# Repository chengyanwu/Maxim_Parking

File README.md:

# SpotOn

Description
-----------
Finding parking spots is an issue that plagues every driver. SpotOn addresses this problem by proposing an intelligent parking sensor system powered by ML image recognition. Using an onboard CNN accelerator with a microcontroller, parking spot detection can be accomplished with low cost and low power consumption. Spot statuses are sent to a central database through LoRaWAN communication and rendered on a web application for users to easily access.

Website: https://sites.google.com/view/spoton-ucsb/home

### Loading and Running Applications
OpenOCD: 
```bash
openocd -f interface/cmsis-dap.cfg -f target/max78000.cfg -s/c/MaximSDK/Tools/OpenOCD/scripts```
GDB:
```bash
arm-none-eabi-gdb max78000.elf
```
```bash
target remote localhost:3333
monitor reset halt
load
compare-sections
monitor reset halt
c
```

## LoRaWan Configuration
Device ID:
```bash
static const PROGMEM u1_t NWKSKEY[16] = { 0x82, 0xDE, 0xD9, 0x1D, 0x69, 0x58, 0xF3, 0x66, 0xBA, 0x3A, 0x8E, 0x15, 0x77, 0xA7, 0xAB, 0xD8 };  
static const u1_t PROGMEM APPSKEY[16] = { 0xDA, 0xBF, 0xD5, 0x35, 0x76, 0x48, 0x84, 0x6C, 0x0D, 0x43, 0xBD, 0xC1, 0x96, 0x54, 0x63, 0x91 };
static const u4_t DEVADDR =  0x260C8A4A ;
```

```bash
static const u1_t NWKSKEY[16] = {0x4A, 0x96, 0xDF, 0xBE, 0x3D, 0xC0, 0x7F, 0x02, 0xB3, 0xBB, 0xE2, 0xCA, 0xDB, 0x84, 0x70, 0x41};
static const u1_t APPSKEY[16] = {0x6C, 0xC5, 0x3C, 0xF2, 0x0D, 0x9A, 0x03, 0x94, 0xAB, 0x31, 0xA4, 0xE4, 0xF9, 0xE0, 0x36, 0x4F};
static const u4_t DEVADDR = 0x260CA619;
```

```bash
static const u1_t NWKSKEY[16] = {0x3A, 0x9C, 0x5C, 0x34, 0x56, 0x0C, 0x73, 0xC4, 0xF7, 0x27, 0x45, 0xDD, 0xD3, 0xC3, 0xD8, 0x9C};
static const u1_t APPSKEY[16] = {0xCE, 0xEE, 0xC9, 0x2B, 0xEB, 0x2A, 0xA8, 0x45, 0xAD, 0x2A, 0x1A, 0x33, 0x1A, 0xCC, 0xC6, 0x39};
static const u4_t DEVADDR = 0x260C6455;
```

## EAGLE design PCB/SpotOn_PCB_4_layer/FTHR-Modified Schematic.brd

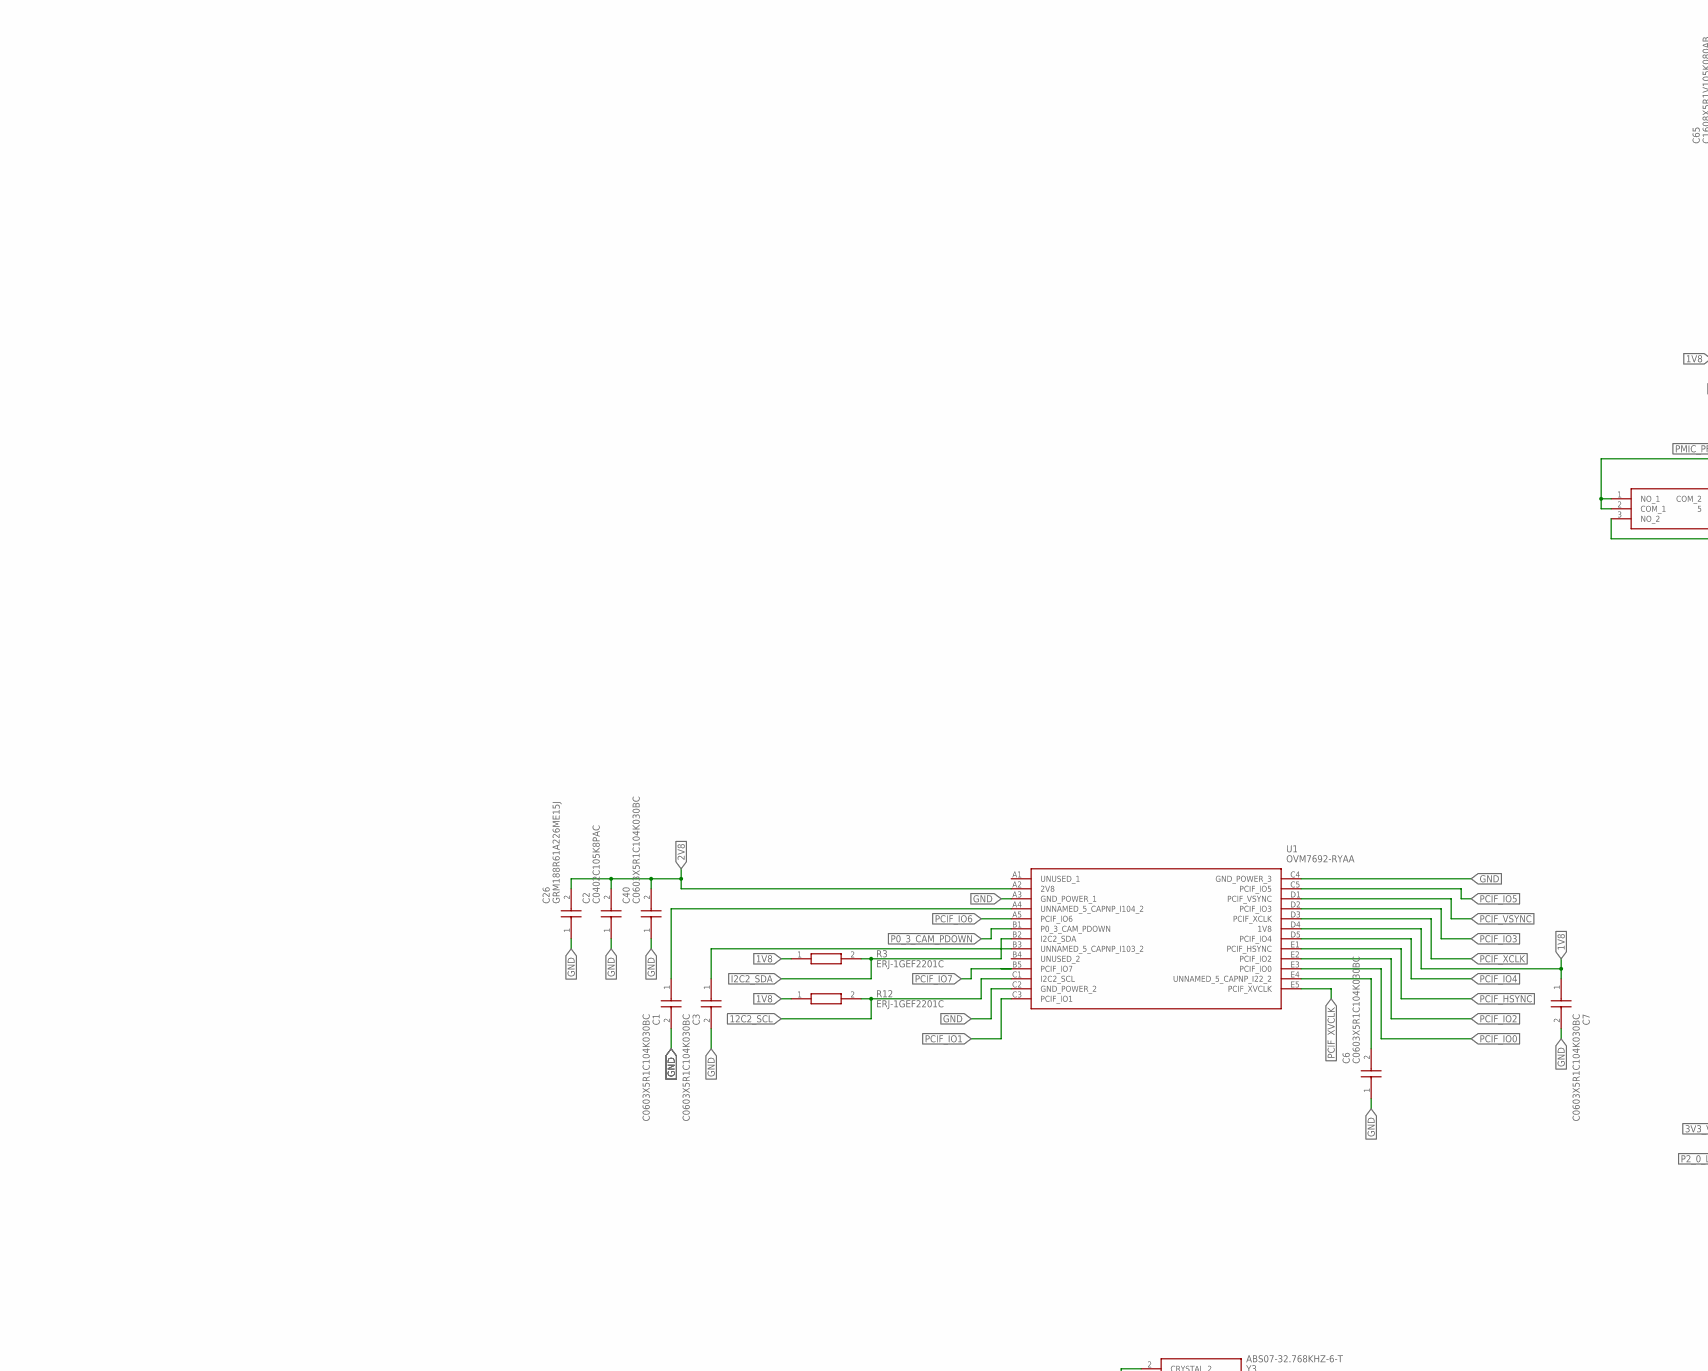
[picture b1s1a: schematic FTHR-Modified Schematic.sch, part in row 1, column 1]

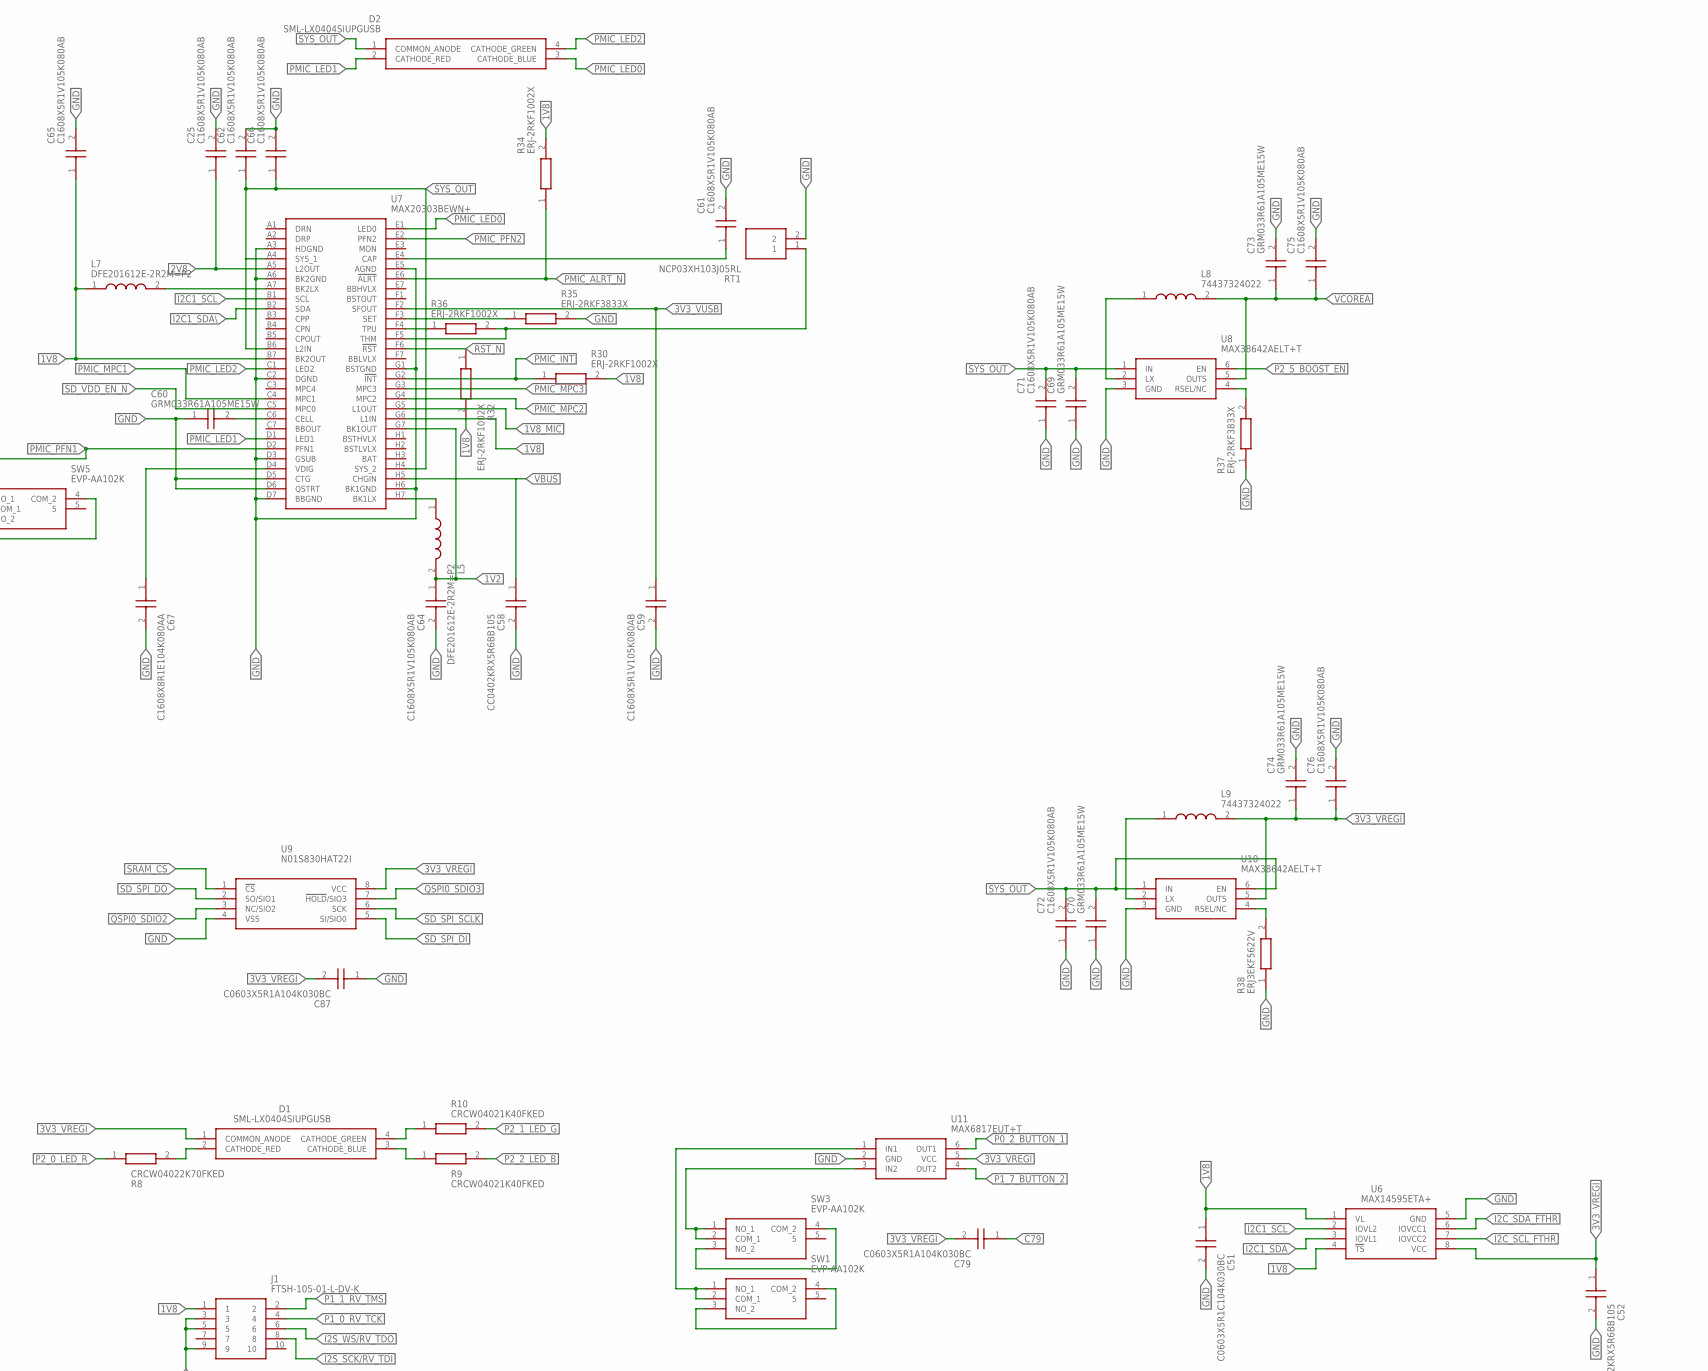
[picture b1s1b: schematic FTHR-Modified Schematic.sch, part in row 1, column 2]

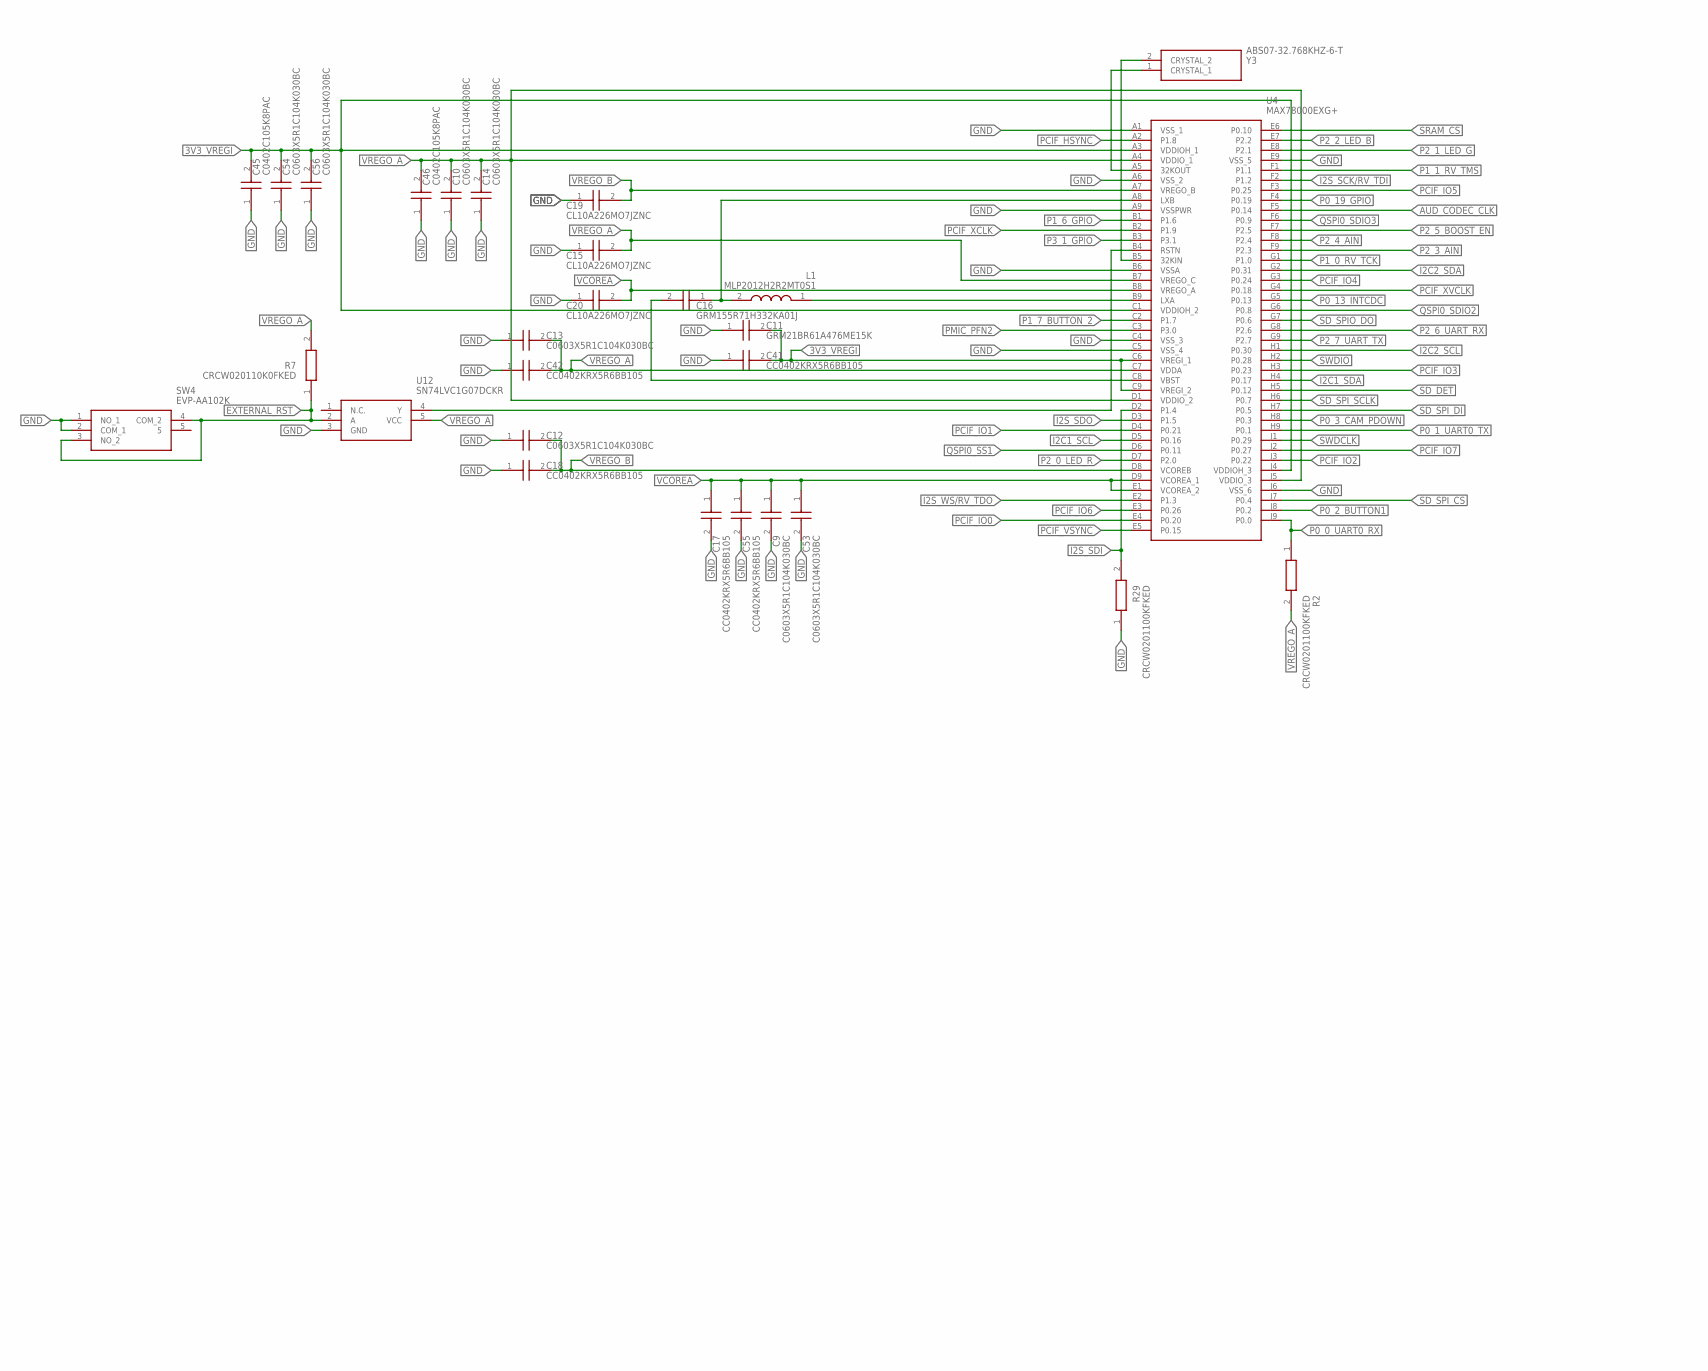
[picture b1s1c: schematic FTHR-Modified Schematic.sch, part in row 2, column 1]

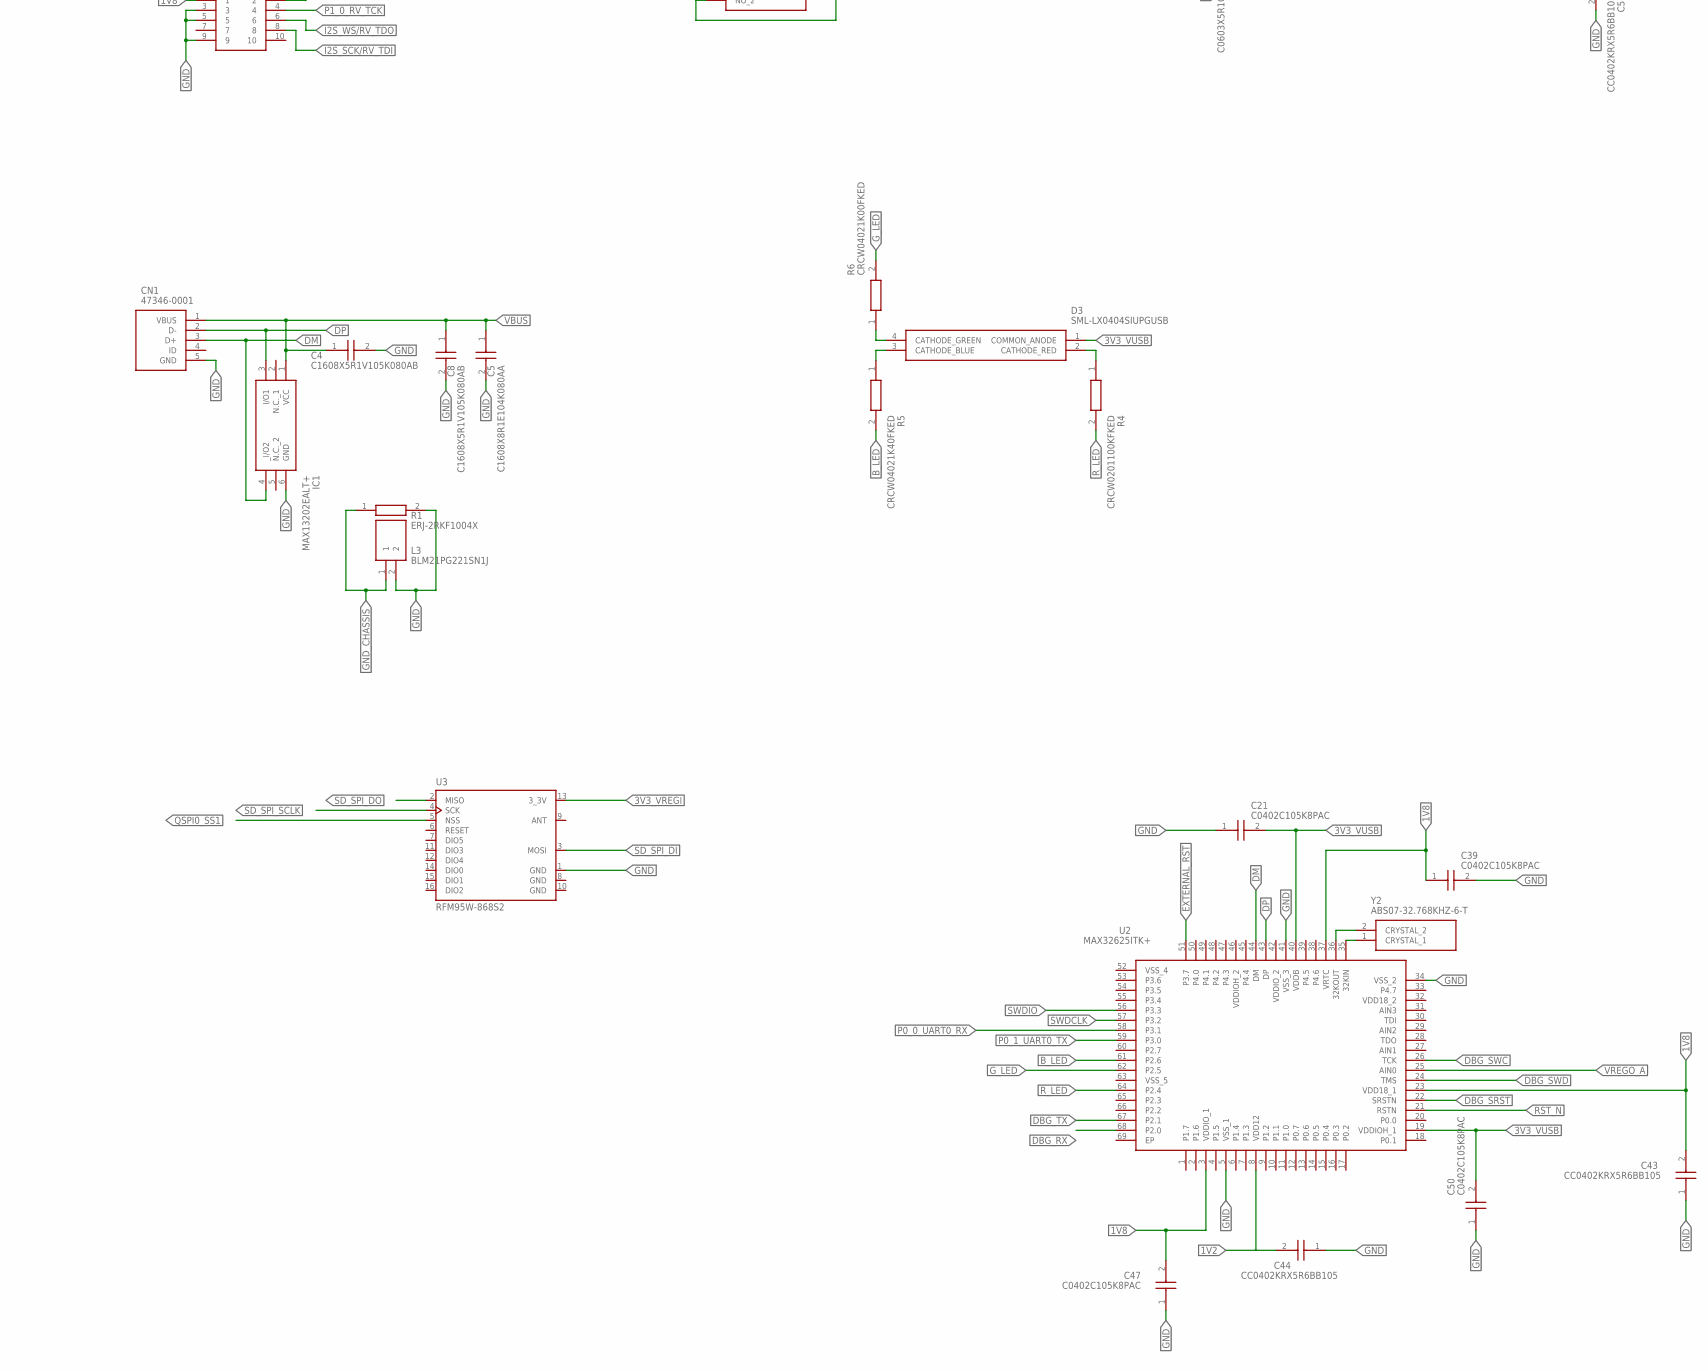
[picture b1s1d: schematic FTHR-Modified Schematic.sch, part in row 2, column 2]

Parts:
C1, C3, C6, C7, C9, C10, C12, C13, C14, C40, C51, C53, C54, C56: C0603X5R1C104K030BC; C0603_COMMERCIAL
C2, C21, C39, C45, C46, C47, C50: C0402C105K8PAC; CAPC1005X55N
C4, C8, C25, C59, C61, C62, C64, C65, C66, C71, C72, C75, C76: C1608X5R1V105K080AB; C1608_COMMERCIAL
C5, C67: C1608X8R1E104K080AA; C1608_COMMERCIAL
C11: GRM21BR61A476ME15K; CAPC2012X145N
C15, C19, C20: CL10A226MO7JZNC; CAPC1608X80N
C16: GRM155R71H332KA01J; CAPC1005X55N
C17, C18, C41, C42, C43, C44, C52, C55, C58: CC0402KRX5R6BB105; CAPC1005X55N
C26: GRM188R61A226ME15J; CAPC1608X90N
C60, C69, C70, C73, C74: GRM033R61A105ME15W; CAPC0603X33N
C79, C87: C0603X5R1A104K030BC; C0603_COMMERCIAL
CN1: 47346-0001
D1, D2, D3: SML-LX0404SIUPGUSB
IC1: MAX13202EALT+; MAX13202EALT
J1: FTSH-105-01-L-DV-K; FTSH10501LDVK
L1: MLP2012H2R2MT0S1; INDC2012X105N
L3: BLM21PG221SN1J; BLM21AG102BH1J
L5, L7: DFE201612E-2R2M=P2; 1286ASH1R0MP2
L8, L9: 74437324022; WE-LHMI_402048
R1: ERJ-2RKF1004X; ERJ2R_(0402)
R2, R4, R29: CRCW0201100KFKED; RESC0603X28N
R3, R12: ERJ-1GEF2201C; RESC0603X26N
R5, R9, R10: CRCW04021K40FKED; RESC1005X40N
R6: CRCW04021K00FKED; RESC1005X40N
R7: CRCW020110K0FKED; RESC0603X28N
R8: CRCW04022K70FKED; RESC1005X40N
R30, R32, R34, R36: ERJ-2RKF1002X; ERJ2R_(0402)
R35, R37: ERJ-2RKF3833X; ERJ2R_(0402)
R38: ERJ3EKF5622V; ERJ3EK_(0603)
RT1: NCP03XH103J05RL; THRMC0603X33N
SW1, SW3, SW4, SW5: EVP-AA102K; EVPAA102K
U1: OVM7692-RYAA; BGA25C50P5X5_347000X295000X276
U2: MAX32625ITK+; QFN40P800X800X80-69N
U3: RFM95W-868S2; XCVR_RFM95W-868S2
U4: MAX78000EXG+; BGA81C80P9X9_800X800X130
U6: MAX14595ETA+; MAX14595ETA
U7: MAX20303BEWN+; BGA56C50P7X8_368X418X69
U8, U10: MAX38642AELT+T; MAX38642AELTT
U9: N01S830HAT22I; SOP65P640X110-8N
U11: MAX6817EUT+T; SOT95P280X145-6N
U12: SN74LVC1G07DCKR; SOT65P210X110-5N
Y2, Y3: ABS07-32.768KHZ-6-T; ABS0732768KHZ6T

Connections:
1V2: C44.2, C64.1, L5.2, U2.8 (VDD12), U7.G7 (BK1OUT)
1V8: C7.1, C39.1, C43.2, C47.2, C51.1, C65.1, J1.1, L7.1, R3.1, R12.1, R30.2, R32.2, R34.2, U1.D4 (1V8), U2.3 (VDDIO_1), U2.23 (VDD18_1), U2.37 (VRTC), U6.1 (VL), U6.4 (!TS), U7.B7 (BK2OUT), U7.G6 (L1IN)
1V8_MIC: U7.G5 (L1OUT)
2V8: C2.2, C25.1, C26.2, C40.2, U1.A2 (2V8), U7.A5 (L2OUT)
3V3_VREGI: C11.2, C41.2, C45.2, C52.1, C54.2, C56.2, C74.1, C76.1, C79.2, C87.2, D1.1 (COMMON_ANODE), L9.2, U3.13 (3_3V), U4.A3 (VDDIOH_1), U4.C1 (VDDIOH_2), U4.C6 (VREGI_1), U4.C9 (VREGI_2), U4.J4 (VDDIOH_3), U6.8 (VCC), U9.8 (VCC), U10.5 (OUTS), U11.5 (VCC)
3V3_VUSB: C21.2, C50.2, C59.1, D3.1 (COMMON_ANODE), U2.19 (VDDIOH_1), U2.40 (VDDB), U7.F2 (SFOUT)
12C2_SCL: R12.2, U1.C1 (I2C2_SCL)
AUD_CODEC_CLK: U4.F5 (P0.14)
B_LED: R5.2, U2.61 (P2.6)
C79: C79.1
DBG_RX: U2.68 (P2.0)
DBG_SRST: U2.22 (SRSTN)
DBG_SWC: U2.26 (TCK)
DBG_SWD: U2.24 (TMS)
DBG_TX: U2.67 (P2.1)
DM: CN1.3 (D+), IC1.4 (_I/O2), U2.44 (DM)
DP: CN1.2 (D-), IC1.3 (I/O1), U2.43 (DP)
EXTERNAL_RST: R7.1, SW4.3 (NO_2), SW4.4 (COM_2), U2.51 (P3.7), U12.2 (A)
GND: C1.2, C2.1, C3.2, C4.2, C5.2, C6.1, C7.2, C8.2, C9.2, C10.1, C11.1, C13.1, C14.1, C15.1, C17.2, C19.1, C20.1, C21.1, C25.2, C26.1, C39.2, C40.1, C41.1, C42.1, C43.1, C44.1, C45.1, C46.1, C47.1, C50.1, C51.2, C52.2, C53.2, C54.1, C55.2, C56.1, C58.2, C59.2, C60.1, C61.2, C62.2, C64.2, C65.2, C66.2, C67.2, C69.1, C70.1, C71.1, C72.1, C73.2, C74.2, C75.2, C76.2, C87.1, CN1.5 (GND), IC1.6 (GND), J1.3, J1.5, J1.9, L3.2, R1.2, R29.1, R35.1, R35.2, R37.1, R38.1, RT1.2, SW4.1 (NO_1), SW4.2 (COM_1), U1.A3 (GND_POWER_1), U1.C2 (GND_POWER_2), U1.C4 (GND_POWER_3), U2.5 (VSS_1), U2.34 (VSS_2), U2.41 (VSS_3), U3.1 (GND), U3.8 (GND), U3.10 (GND), U4.A1 (VSS_1), U4.A6 (VSS_2), U4.A9 (VSSPWR), U4.B6 (VSSA), U4.C4 (VSS_3), U4.C5 (VSS_4), U4.E9 (VSS_5), U4.J6 (VSS_6), U6.5 (GND), U7.A3 (HDGND), U7.A6 (BK2GND), U7.C2 (DGND), U7.D3 (GSUB), U7.D5 (CTG), U7.D6 (QSTRT), U7.D7 (BBGND), U7.E5 (AGND), U7.F3 (SET), U7.G1 (BSTGND), U7.H6 (BK1GND), U8.3 (GND), U9.4 (VSS), U10.3 (GND), U11.2 (GND), U12.3 (GND)
GND_CHASSIS: L3.1, R1.1
G_LED: R6.2, U2.62 (P2.5)
I2C1_SCL: U4.D5 (P0.16), U6.2 (IOVL2), U7.B1 (SCL)
I2C1_SDA: U4.H4 (P0.17), U6.3 (IOVL1)
I2C1_SDA\: U7.B2 (SDA)
I2C2_SCL: U4.H1 (P0.30)
I2C2_SDA: R3.2, U1.B2 (I2C2_SDA), U4.G2 (P0.31)
I2C_SCL_FTHR: U6.7 (IOVCC2)
I2C_SDA_FTHR: U6.6 (IOVCC1)
I2S_SCK/RV_TDI: J1.8, U4.F2 (P1.2)
I2S_SDI: R29.2, U4.D2 (P1.4)
I2S_SDO: U4.D3 (P1.5)
I2S_WS/RV_TDO: J1.6, U4.E2 (P1.3)
unnamed: SW5.3 (NO_2), SW5.4 (COM_2)
unnamed: C61.1, U7.E4 (CAP)
unnamed: R36.2, RT1.1, U7.F5 (THM)
unnamed: R36.1, U7.F4 (TPU)
unnamed: C67.1, U7.D4 (VDIG)
unnamed: L7.2, U7.A7 (BK2LX)
unnamed: R37.2, U8.4 (RSEL/NC)
unnamed: L5.1, U7.H7 (BK1LX)
unnamed: C60.2, U7.C6 (CELL)
unnamed: L8.1, U8.2 (LX)
unnamed: R38.2, U10.4 (RSEL/NC)
unnamed: L9.1, U10.2 (LX)
unnamed: SW3.1 (NO_1), SW3.2 (COM_1), U11.3 (IN2)
unnamed: SW1.1 (NO_1), SW1.2 (COM_1), U11.1 (IN1)
unnamed: SW3.3 (NO_2), SW3.4 (COM_2)
unnamed: SW1.3 (NO_2), SW1.4 (COM_2)
unnamed: C1.1, U1.A4 (UNNAMED_5_CAPNP_I104_2)
unnamed: C3.1, U1.B3 (UNNAMED_5_CAPNP_I103_2)
unnamed: D3.2 (CATHODE_RED), R4.1
unnamed: U4.A5 (32KOUT), Y3.1 (CRYSTAL_1)
unnamed: C6.2, U1.E4 (UNNAMED_5_CAPNP_I22_2)
unnamed: U4.B5 (32KIN), Y3.2 (CRYSTAL_2)
unnamed: C16.1, L1.2, U4.A8 (LXB)
unnamed: C16.2, U4.C8 (VBST)
unnamed: L1.1, U4.B9 (LXA)
unnamed: U4.B4 (RSTN), U12.4 (Y)
unnamed: U2.35 (32KIN), U2.36 (32KOUT), Y2.1 (CRYSTAL_1), Y2.2 (CRYSTAL_2)
unnamed: D3.3 (CATHODE_BLUE), R5.1
unnamed: D3.4 (CATHODE_GREEN), R6.1
P0_0_UART0_RX: R2.1, U2.58 (P3.1), U4.J9 (P0.0)
P0_1_UART0_TX: U2.59 (P3.0), U4.H9 (P0.1)
P0_2_BUTTON1: U4.J8 (P0.2)
P0_2_BUTTON_1: U11.6 (OUT1)
P0_3_CAM_PDOWN: U1.B1 (P0_3_CAM_PDOWN), U4.H8 (P0.3)
P0_13_INTCDC: U4.G5 (P0.13)
P0_19_GPIO: U4.F4 (P0.19)
P1_0_RV_TCK: J1.4, U4.G1 (P1.0)
P1_1_RV_TMS: J1.2, U4.F1 (P1.1)
P1_6_GPIO: U4.B1 (P1.6)
P1_7_BUTTON_2: U4.C2 (P1.7), U11.4 (OUT2)
P2_0_LED_R: D1.2 (CATHODE_RED), R8.1, R8.2, U4.D7 (P2.0)
P2_1_LED_G: D1.4 (CATHODE_GREEN), R10.1, R10.2, U4.E8 (P2.1)
P2_2_LED_B: D1.3 (CATHODE_BLUE), R9.1, R9.2, U4.E7 (P2.2)
P2_3_AIN: U4.F9 (P2.3)
P2_4_AIN: U4.F8 (P2.4)
P2_5_BOOST_EN: U4.F7 (P2.5), U8.6 (EN)
P2_6_UART_RX: U4.G8 (P2.6)
P2_7_UART_TX: U4.G9 (P2.7)
P3_1_GPIO: U4.B3 (P3.1)
PCIF_HSYNC: U1.E1 (PCIF_HSYNC), U4.A2 (P1.8)
PCIF_IO0: U1.E3 (PCIF_IO0), U4.E4 (P0.20)
PCIF_IO1: U1.C3 (PCIF_IO1), U4.D4 (P0.21)
PCIF_IO2: U1.E2 (PCIF_IO2), U4.J3 (P0.22)
PCIF_IO3: U1.D2 (PCIF_IO3), U4.H3 (P0.23)
PCIF_IO4: U1.D5 (PCIF_IO4), U4.G3 (P0.24)
PCIF_IO5: U1.C5 (PCIF_IO5), U4.F3 (P0.25)
PCIF_IO6: U1.A5 (PCIF_IO6), U4.E3 (P0.26)
PCIF_IO7: U1.B5 (PCIF_IO7), U4.J2 (P0.27)
PCIF_VSYNC: U1.D1 (PCIF_VSYNC), U4.E5 (P0.15)
PCIF_XCLK: U1.D3 (PCIF_XCLK), U4.B2 (P1.9)
PCIF_XVCLK: U1.E5 (PCIF_XVCLK), U4.G4 (P0.18)
PMIC_ALRT_N: R34.1, U7.E6 (!ALRT)
PMIC_INT: R30.1, U7.G2 (!INT)
PMIC_LED0: D2.3 (CATHODE_BLUE), U7.E1 (LED0)
PMIC_LED1: D2.2 (CATHODE_RED), U7.D1 (LED1)
PMIC_LED2: D2.4 (CATHODE_GREEN), U7.C1 (LED2)
PMIC_MPC1: U7.C4 (MPC1)
PMIC_MPC2: U7.G4 (MPC2)
PMIC_MPC3: U7.G3 (MPC3)
PMIC_PFN1: SW5.1 (NO_1), SW5.2 (COM_1), U7.D2 (PFN1)
PMIC_PFN2: U4.C3 (P3.0), U7.E2 (PFN2)
QSPI0_SDIO2: U4.G6 (P0.8), U9.3 (NC/SIO2)
QSPI0_SDIO3: U4.F6 (P0.9), U9.7 (!HOLD!/SIO3)
QSPI0_SS1: U3.5 (NSS), U4.D6 (P0.11)
RST_N: R32.1, U2.21 (RSTN), U7.F6 (!RST)
R_LED: R4.2, U2.64 (P2.4)
SD_DET: U4.H5 (P0.12)
SD_SPIO_DO: U4.G7 (P0.6)
SD_SPI_CS: U4.J7 (P0.4)
SD_SPI_DI: U3.3 (MOSI), U4.H7 (P0.5), U9.5 (SI/SIO0)
SD_SPI_DO: U3.2 (MISO), U9.2 (SO/SIO1)
SD_SPI_SCLK: U3.4 (SCK), U4.H6 (P0.7), U9.6 (SCK)
SD_VDD_EN_N: U7.C5 (MPC0)
SRAM_CS: U4.E6 (P0.10), U9.1 (!CS)
SWDCLK: U2.57 (P3.2), U4.J1 (P0.29)
SWDIO: U2.56 (P3.3), U4.H2 (P0.28)
SYS_OUT: C62.1, C66.1, C69.2, C70.2, C71.2, C72.2, D2.1 (COMMON_ANODE), U7.A4 (SYS_1), U7.B6 (L2IN), U7.H4 (SYS_2), U8.1 (IN), U10.1 (IN), U10.6 (EN)
VBUS: C4.1, C5.1, C8.1, C58.1, CN1.1 (VBUS), IC1.1 (VCC), U7.H5 (CHGIN)
VCOREA: C9.1, C17.1, C20.2, C53.1, C55.1, C73.1, C75.1, L8.2, U4.B8 (VREGO_A), U4.D9 (VCOREA_1), U4.E1 (VCOREA_2), U8.5 (OUTS)
VREGO_A: C10.2, C13.2, C14.2, C15.2, C42.2, C46.2, R2.2, R7.2, U2.25 (AIN0), U4.A4 (VDDIO_1), U4.B7 (VREGO_C), U4.C7 (VDDA), U4.D1 (VDDIO_2), U4.J5 (VDDIO_3), U12.5 (VCC)
VREGO_B: C12.2, C18.2, C19.2, U4.A7 (VREGO_B), U4.D8 (VCOREB)

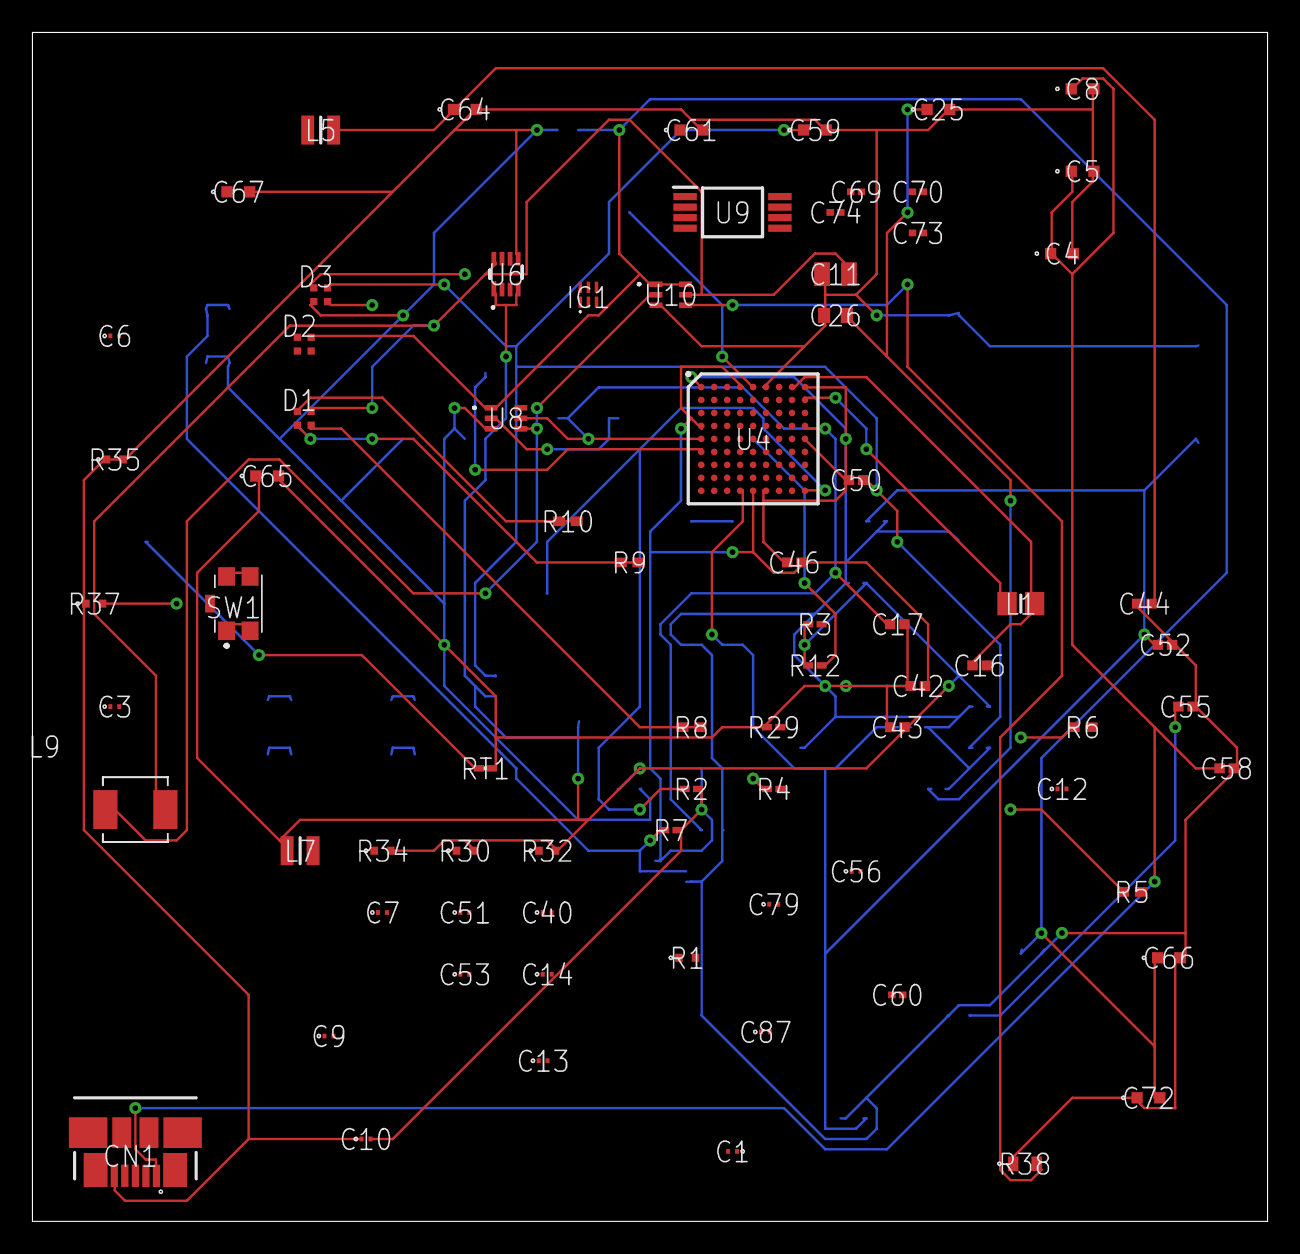
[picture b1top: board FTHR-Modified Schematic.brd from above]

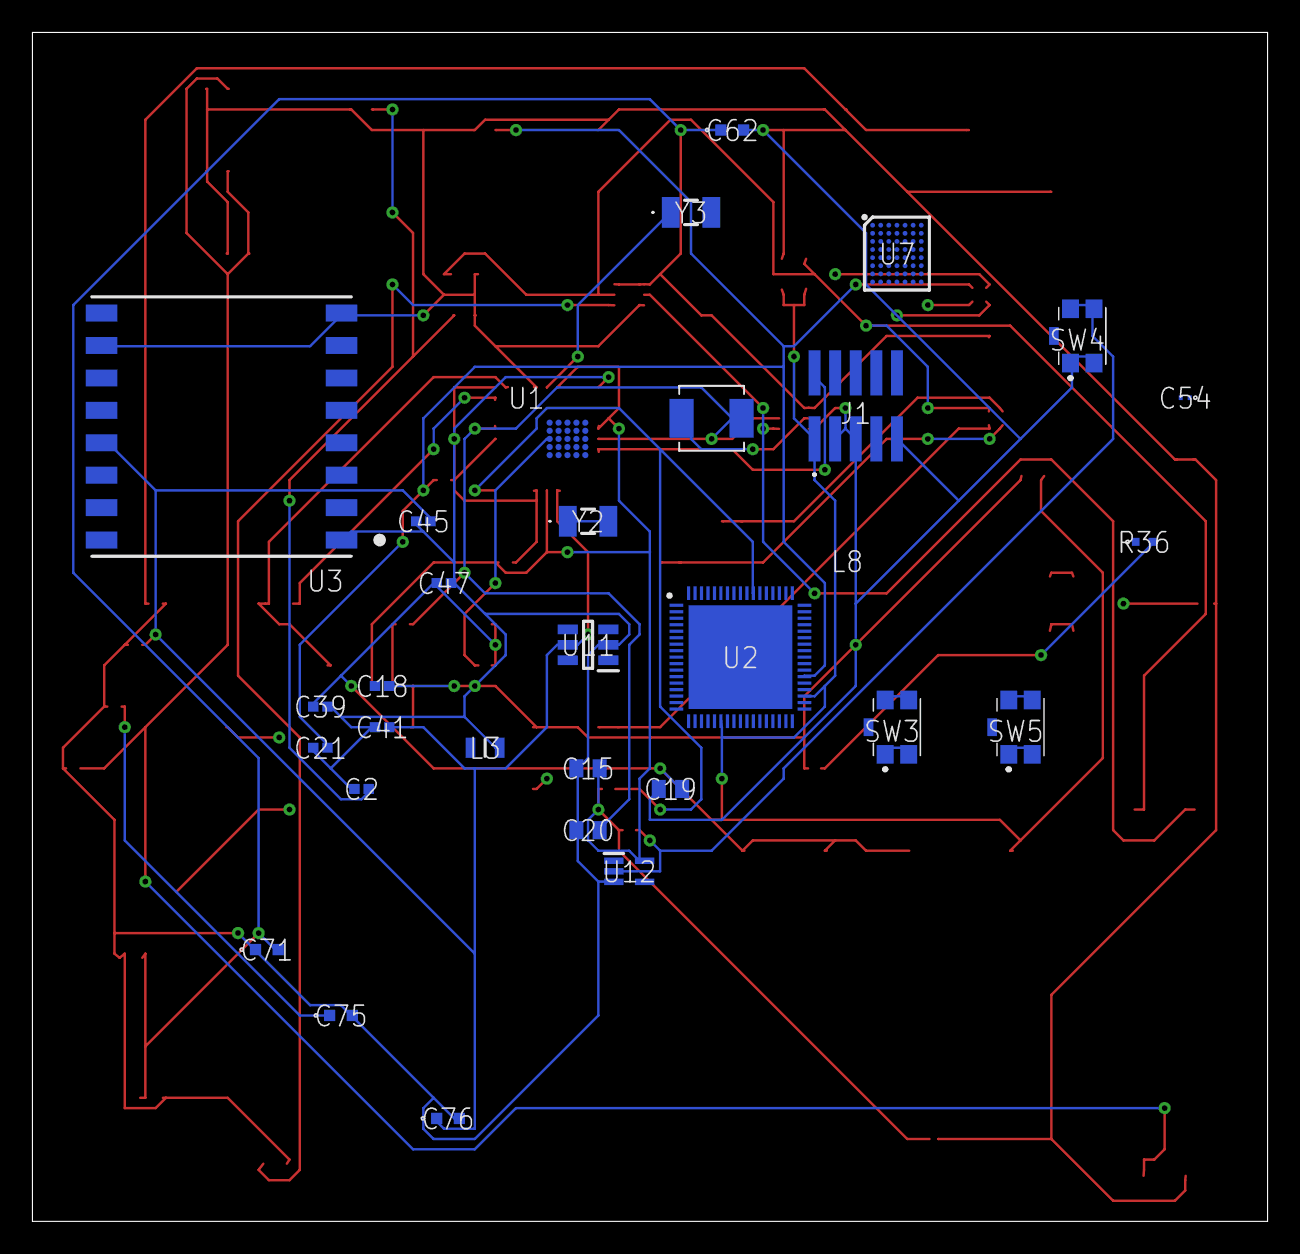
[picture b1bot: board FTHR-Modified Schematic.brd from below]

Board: 4 copper layers, 76.2 x 73.3 mm, 107 parts (30 on the bottom side), 93 nets.

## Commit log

2021-10-25 Create workspace
2021-10-25 created workspace for project app
2021-10-25 added workspace for saving project app
2021-10-25 added library to app
2021-10-26 new cameraIF with lib added
2021-11-01 it can store raw data now
2021-11-01 IW, add MNIST digit recognition program(ML result incorrect)
2021-11-01 IW, added digits recognition program (ML result incorrect)
2021-11-04 mnist with camera
2021-11-05 IW, added featherboard digit reg(CNN_Start failed)
2021-11-09 IW, FTHR can recognize figits, but incorrect
2021-11-12 IW, added car-detection code
2021-11-19 add in libraries
2021-11-19 added ai8x-training
2021-11-19 added training
2021-11-23 added new model
2021-11-30 added car detection model (100 epochs)
2021-12-02 update cameraIF
2021-12-03 add featherboard/lorawan communication files
2021-12-03 add UART code, updated arduino rx/tx code (still need to make messages send/recieve over UART properly)
2021-12-03 added cats-dogs_demo
2022-01-04 added to cameraIF
2022-01-05 build for cameraIF
2022-01-05 added cameraIF builds
2022-01-05 added CameraIF build
2022-01-09 added simple image segmenting tool in util.c
2022-01-14 update cats-dogs_demo
2022-01-15 Car Detection Evkit working
2022-01-17 added image segmenting on dog-cat-demo
2022-01-18 Evkit Library updated
2022-01-18 no change
2022-01-18 evkit library update
2022-01-20 image segmentation sync
2022-01-20 seg syn
2022-01-20 segmentation working
2022-01-20 seg code clean up
2022-01-21 add new build to cameraif
2022-01-21 cat_dog_demo_565
2022-01-25 fix bugs to make it runnable
2022-01-27 add conversion from 565 to 888
2022-01-28 change folder names
2022-01-28 rgb888 seg working on evkit
2022-01-30 create car_detection_w_LoRa
2022-02-01 segmenting_565
2022-02-01 lora-detection
2022-02-01 add LoRa with 565seg
2022-02-05 debug UART communication
2022-02-05 mod detection_w_LorA
2022-02-08 debug uart noise
2022-02-08 add second node address
2022-02-10 detection+lora
2022-02-10 add basic code to read application traffic from ttn
2022-02-10 detection with lora working, but noisy datas
2022-02-12 fix UART noise and add UART to seg4
2022-02-17 added python script
2022-02-19 add display to camera app
2022-02-19 working uart and lora
2022-02-19 readme update
2022-02-24 save model input images and results
2022-02-24 save model input image and result
2022-02-26 added rfm95w example
2022-03-03 added lmic library to max78000
2022-03-03 added LMIC lib to max78000
2022-03-03 clean up hal.c for max78000
2022-03-03 added hal function for max78000
2022-03-04 modified main
2022-03-06 lora
2022-03-16 spi config for max78000
2022-03-30 lora init working
2022-04-01 lora working
2022-04-01 changed makefile for lmic
2022-04-01 add rfm95w + lora with SPI
2022-04-08 new model
2022-04-08 org code
2022-04-08 organized files
2022-04-11 move camera
2022-04-15 lora to camera
2022-04-18 lora + tft + camera
2022-04-18 tft+ lora working
2022-04-18 added lora tft config to car detection
2022-04-25 changed made
2022-04-26 add tft lora to car detection
2022-04-28 added poster
2022-05-02 update poster
2022-05-02 poster update
2022-05-04 modify lib/car detection program
2022-05-05 poster upd
2022-05-05 nothing added
2022-05-08 changed cnn load input
2022-05-12 poster
2022-05-13 poster updated
2022-05-16 low power
2022-06-03 upload cad file
2022-06-03 add PCB file
2022-12-12 Adding tarfile member sanitization to extractall()
